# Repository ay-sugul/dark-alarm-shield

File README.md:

# Dark Alarm Shield v1.0

A 2-layer Arduino UNO shield that sounds a buzzer when the ambient light drops below a threshold.
Designed end-to-end in **KiCad 10**: schematic → ERC → footprints → PCB layout → DRC → Gerber/drill output.

## Overview

| | |
|---|---|
| Form factor | Arduino UNO shield, 69 × 54 mm |
| Layers | 2 (signals on F.Cu, GND copper pour on B.Cu) |
| Sensor | LDR in a voltage divider with a 10 kΩ resistor → analog input |
| Output | Buzzer on digital pin D8 |
| Components | All through-hole (R1 10 kΩ, R2 LDR, BZ1 buzzer) |
| Design rules | 0.25 mm minimum track width / clearance; signal tracks 0.4 mm |
| Tool | KiCad 10 |

## Repository structure

```
hardware/   KiCad project (.kicad_pro, .kicad_sch, .kicad_pcb)
fab/        Gerber files, PTH/NPTH Excellon drill files, .gbrjob (zipped)
docs/       Schematic PDF, 3D renders, BOM
firmware/   Arduino sketch
```

## Design decisions

- **Shield form factor:** the board plugs directly onto an Arduino UNO, so no extra wiring is needed.
- **GND pour on the bottom layer:** all signal routing stays on the top layer and the bottom layer is a continuous ground plane. This gives a low-impedance return path and makes routing simpler.
- **0.4 mm signal tracks:** wider than the 0.25 mm minimum, for easier manufacturing and more robust traces at no cost on a board this size.
- **Footprints chosen to match real parts:**
  - R1: `R_Axial_DIN0207_L6.3mm_D2.5mm_P2.54mm_Vertical`
  - R2 (LDR): `R_LDR_4.9x4.2mm_P2.54mm_Vertical`
  - BZ1: `Buzzer_12x9.5RM7.6`

## Problems I solved

| Problem | What I did |
|---|---|
| ERC errors on unconnected pins and power nets | Added no-connect flags and `PWR_FLAG` symbols → 0 ERC violations |
| DRC clearance violation near the A0 trace | Re-routed the trace |
| Some tracks were 0.2 mm (below my design rule) | Widened them to 0.4 mm |
| Duplicate rectangle on Edge.Cuts | Removed the extra outline so the board has a single closed edge |
| Courtyard warnings caused by the shield headers | Checked them one by one and excluded the false positives |
| Silkscreen clipped by pads | Reviewed the warnings and left the harmless ones on purpose |

## Manufacturing outputs

- 7 Gerber layers + PTH and NPTH Excellon drill files + `.gbrjob`
- Checked in KiCad GerbView before zipping
- Silkscreen includes the board name/version and the buzzer polarity (+) mark

## Firmware

`firmware/dark_alarm.ino` reads the LDR voltage on the analog input and turns the buzzer on when the reading crosses a threshold.

## What I learned

- The full PCB flow in KiCad, from schematic capture to fabrication files
- How design rules and net classes are set up, and how to read and fix ERC/DRC reports
- What a PCB manufacturer expects (Gerber layers, drill files, board outline)

## License

Hardware: [CERN-OHL-S-2.0](https://ohwr.org/cern_ohl_s_v2.txt) · Firmware: MIT

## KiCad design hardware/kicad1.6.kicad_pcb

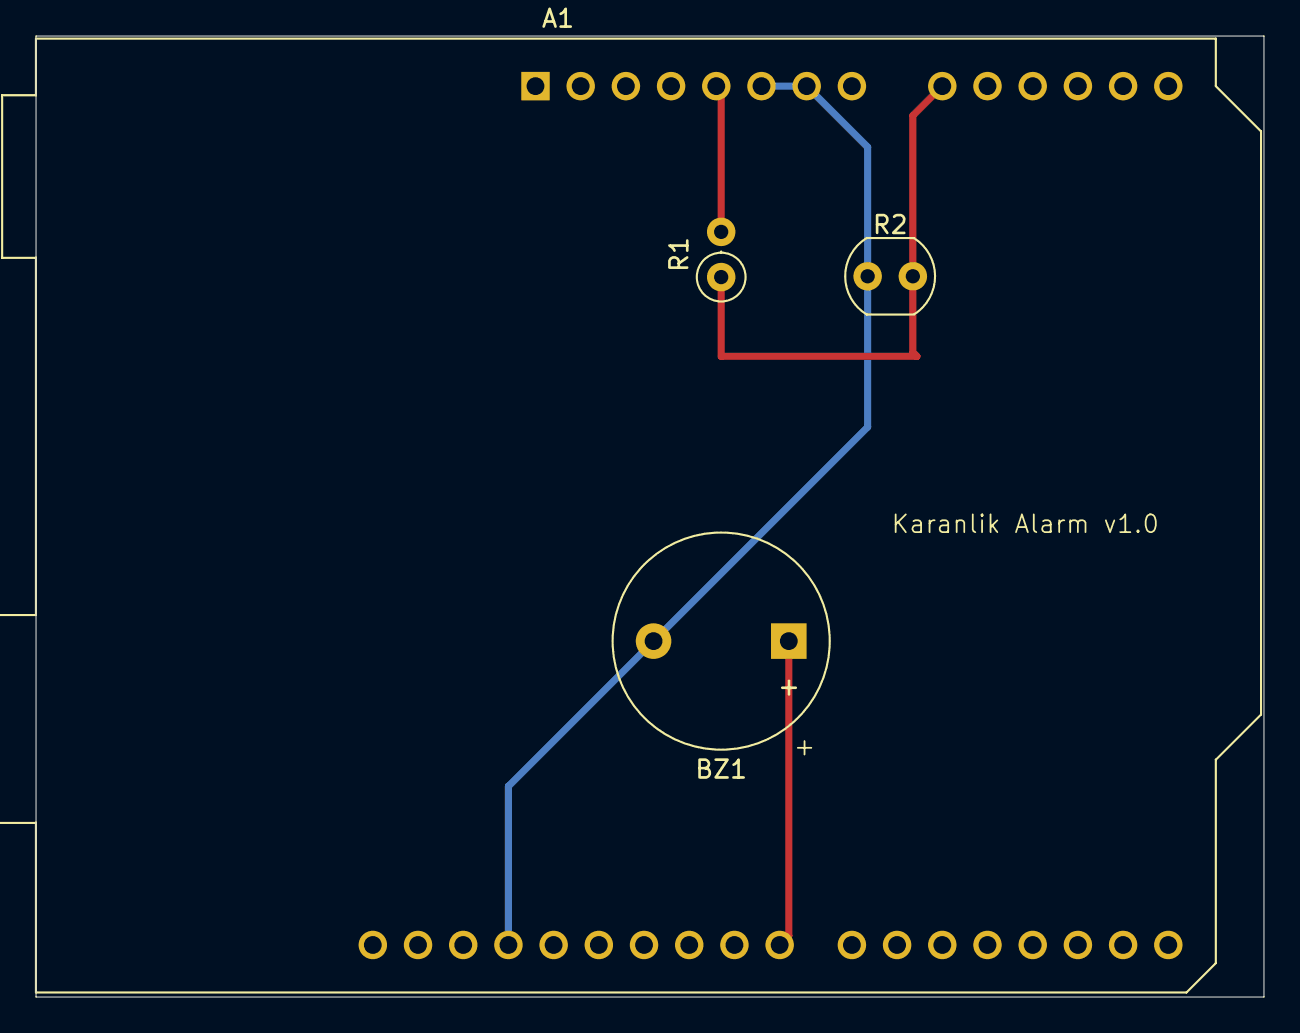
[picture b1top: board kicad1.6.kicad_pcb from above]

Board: 2 copper layers, 69.0 x 54.0 mm, 4 parts (0 on the bottom side), 4 nets.

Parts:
A1: Arduino_UNO_R3
BZ1: Buzzer; Buzzer_12x9.5RM7.6
R1: 10k; R_Axial_DIN0207_L6.3mm_D2.5mm_P2.54mm_Vertical
R2: LDR; R_LDR_4.9x4.2mm_P2.54mm_Vertical

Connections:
+5V: A1.5 (+5V), R1.2
GNDREF: A1.6 (GND), A1.7 (GND), A1.29 (GND), BZ1.2 (-), R2.1
unnamed: A1.9 (A0), R1.1, R2.2
unnamed: A1.23 (D8), BZ1.1 (+)
